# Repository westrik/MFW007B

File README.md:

# MFW007B
NA-01 Rev B (for JLCPCB assembly)

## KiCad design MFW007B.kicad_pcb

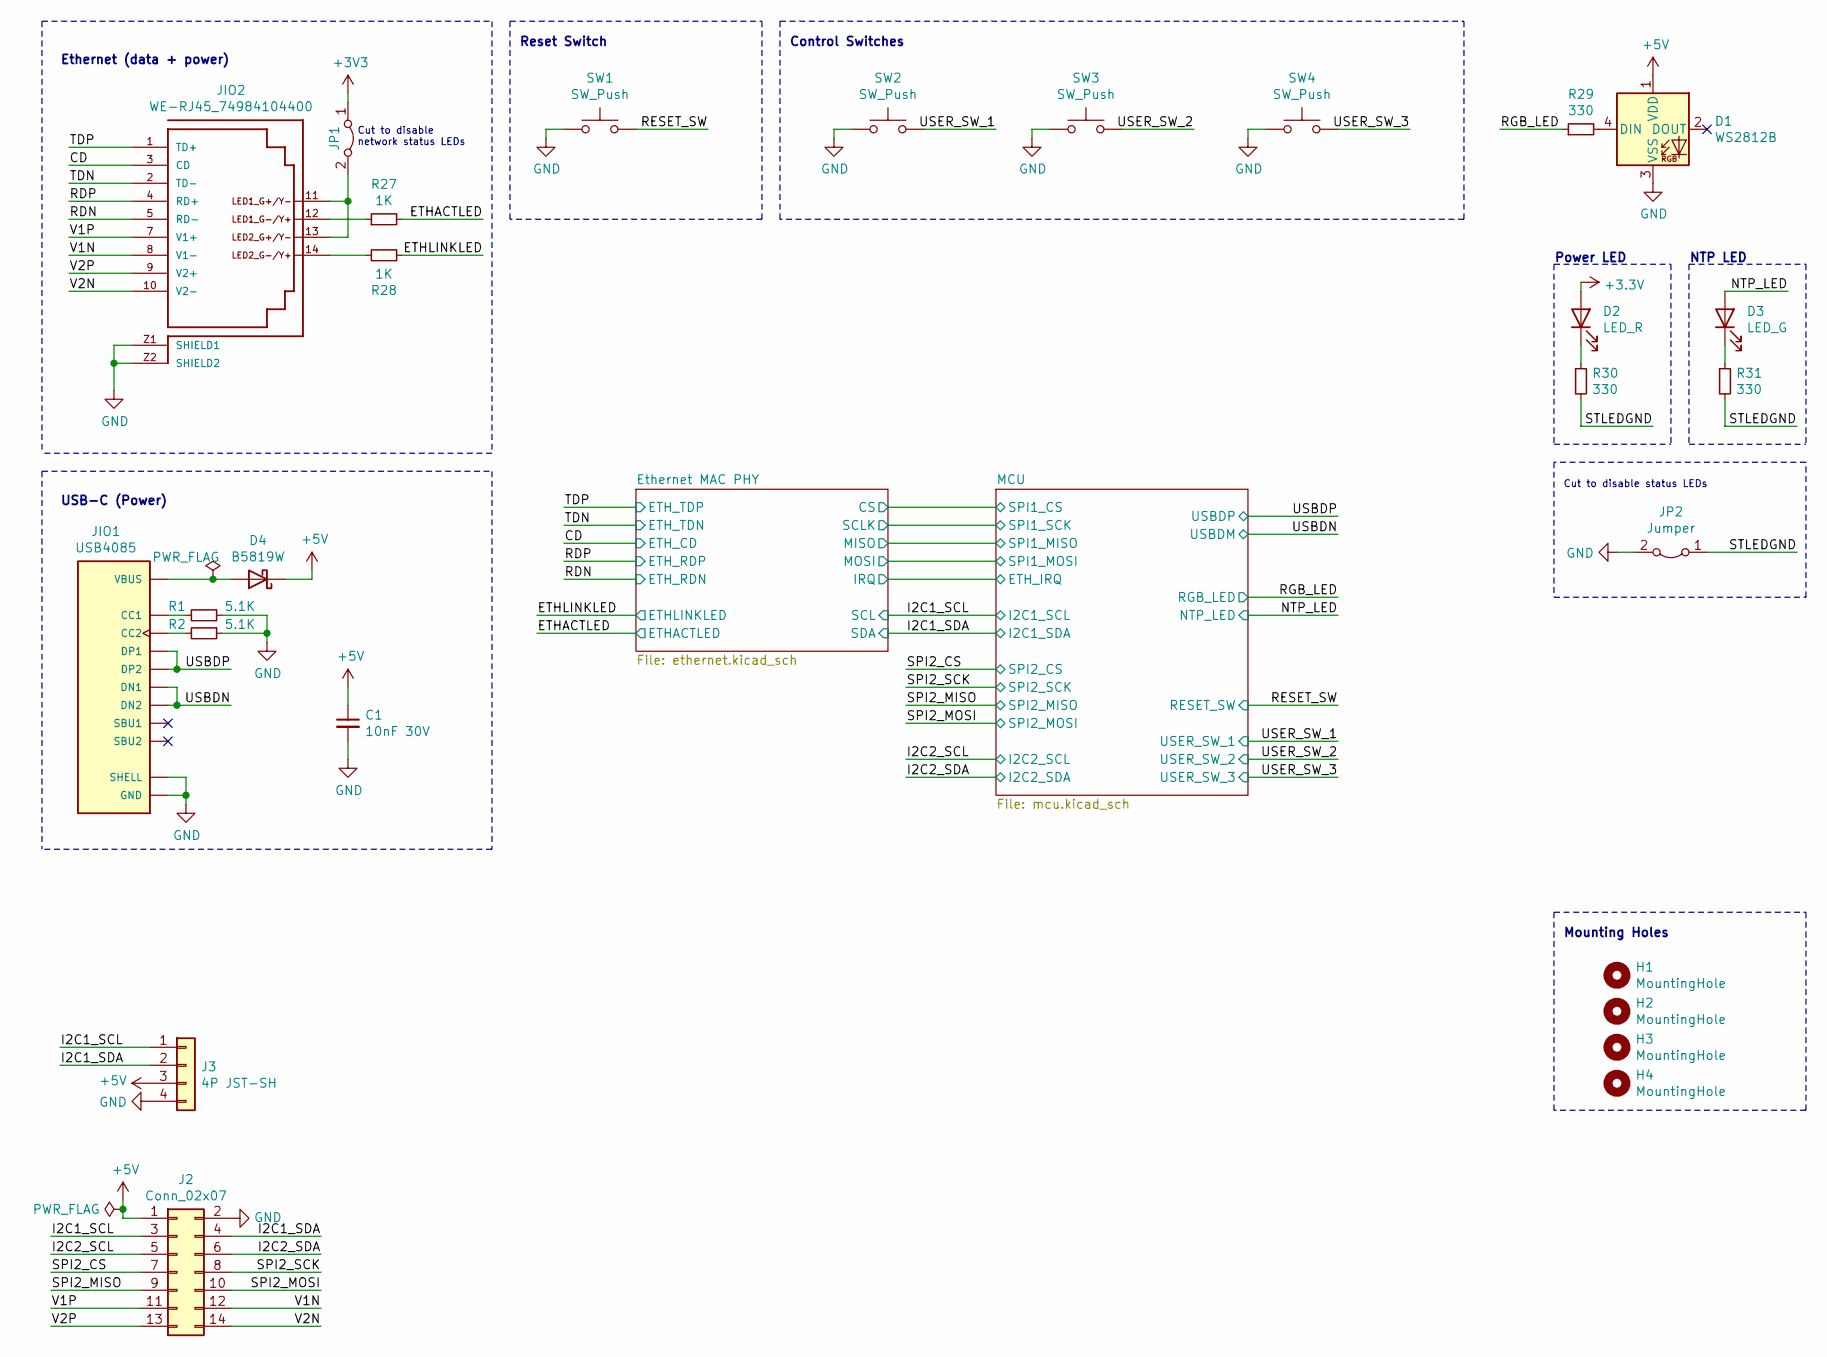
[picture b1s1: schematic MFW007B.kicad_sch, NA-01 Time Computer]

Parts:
C1: 10nF 30V; C_0805_2012Metric; LCSC Part Number C1710
D1: WS2812B; LED_WS2812B_PLCC4_5.0x5.0mm_P3.2mm; LCSC Part Number N/A
D2: LED_R; LED_0603_1608Metric; LCSC Part Number C2286
D3: LED_G; LED_0603_1608Metric; LCSC Part Number C72043
D4: B5819W; D_SOD-123; LCSC Part Number C8598
H1, H2, H3, H4: MountingHole; MountingHole_2.7mm_M2.5; LCSC Part Number N/A
J2: Conn_02x07; PinHeader_2x07_P2.54mm_Vertical; LCSC Part Number N/A
J3: 4P JST-SH; JST_SH_SM04B-SRSS-TB_1x04-1MP_P1.00mm_Horizontal; LCSC Part Number N/A
JIO1: USB4085; GCT_USB4085-GF-A_REVA; Manufacturer Part Number green/yellow-green/yellow; LCSC Part Number N/A
JIO2: WE-RJ45_74984104400; 74984104400; PART-NUMBER 74984104400; LCSC Part Number N/A
JP1, JP2: Jumper; SolderJumper-2_P1.3mm_Bridged_RoundedPad1.0x1.5mm; LCSC Part Number N/A
R1, R2: 5.1K; R_0402_1005Metric; LCSC Part Number C25905
R27, R28: 1K; R_0402_1005Metric
R29, R30, R31: 330; R_0402_1005Metric
SW1, SW2, SW3, SW4: SW_Push; PTS647SK38SMTR2LFS; LCSC Part Number N/A

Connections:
+5V: C1.1, D1.1 (VDD), D4.1 (K), J2.1, J3.3; also elsewhere on the board
/CD: JIO2.3 (CD); also elsewhere on the board
/ETHACTLED: R27.2; also elsewhere on the board
/ETHLINKLED: R28.1; also elsewhere on the board
/I2C1_SCL: J2.3, J3.1; also elsewhere on the board
/I2C1_SDA: J2.4, J3.2; also elsewhere on the board
/I2C2_SCL: J2.5; also elsewhere on the board
/I2C2_SDA: J2.6; also elsewhere on the board
/NTP_LED: D3.2 (A); also elsewhere on the board
/RDN: JIO2.5 (RD-); also elsewhere on the board
/RDP: JIO2.4 (RD+); also elsewhere on the board
/RESET_SW: SW1.2; also elsewhere on the board
/RGB_LED: R29.1; also elsewhere on the board
/SPI2_CS: J2.7; also elsewhere on the board
/SPI2_MISO: J2.9; also elsewhere on the board
/SPI2_MOSI: J2.10; also elsewhere on the board
/SPI2_SCK: J2.8; also elsewhere on the board
/STLEDGND: JP2.1 (A), R30.2, R31.2
/TDN: JIO2.2 (TD-); also elsewhere on the board
/TDP: JIO2.1 (TD+); also elsewhere on the board
/USBDN: JIO1.A7 (DN1), JIO1.B7 (DN2); also elsewhere on the board
/USBDP: JIO1.A6 (DP1), JIO1.B6 (DP2); also elsewhere on the board
/USER_SW_1: SW2.2; also elsewhere on the board
/USER_SW_2: SW3.2; also elsewhere on the board
/USER_SW_3: SW4.2; also elsewhere on the board
/V1N: J2.12, JIO2.8 (V1-)
/V1P: J2.11, JIO2.7 (V1+)
/V2N: J2.14, JIO2.10 (V2-)
/V2P: J2.13, JIO2.9 (V2+)
GND: C1.2, D1.3 (VSS), J2.2, J3.4, JIO1.A1 (GND), JIO1.A12 (GND), JIO1.B1 (GND), JIO1.B12 (GND), JIO1.P1 (SHELL), JIO1.P2 (SHELL), JIO1.P3 (SHELL), JIO1.P4 (SHELL), JIO2.Z1 (SHIELD1), JIO2.Z2 (SHIELD2), JP2.2 (B), R1.1, R2.1, SW1.1, SW2.1, SW3.1, SW4.1; also elsewhere on the board
unnamed: D1.4 (DIN), R29.2
unnamed: D2.1 (K), R30.1
unnamed: D3.1 (K), R31.1
unnamed: D4.2 (A), JIO1.A4 (VBUS), JIO1.A9 (VBUS), JIO1.B4 (VBUS), JIO1.B9 (VBUS)
unnamed: JIO1.A5 (CC1), R1.2
unnamed: JIO1.B5 (CC2), R2.2
unnamed: JIO2.11, JIO2.13, JP1.2 (B)
unnamed: JIO2.12, R27.1
unnamed: JIO2.14, R28.2
no_connect_(D1-Pad2): D1.2 (DOUT)
no_connect_(JIO1-PadA8): JIO1.A8 (SBU1)
no_connect_(JIO1-PadB8): JIO1.B8 (SBU2)

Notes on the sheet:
Ethernet (data + power)
USB-C (Power)
Cut to disable network status LEDs
Reset Switch
Control Switches
Power LED
Cut to disable status LEDs
Mounting Holes
NTP LED

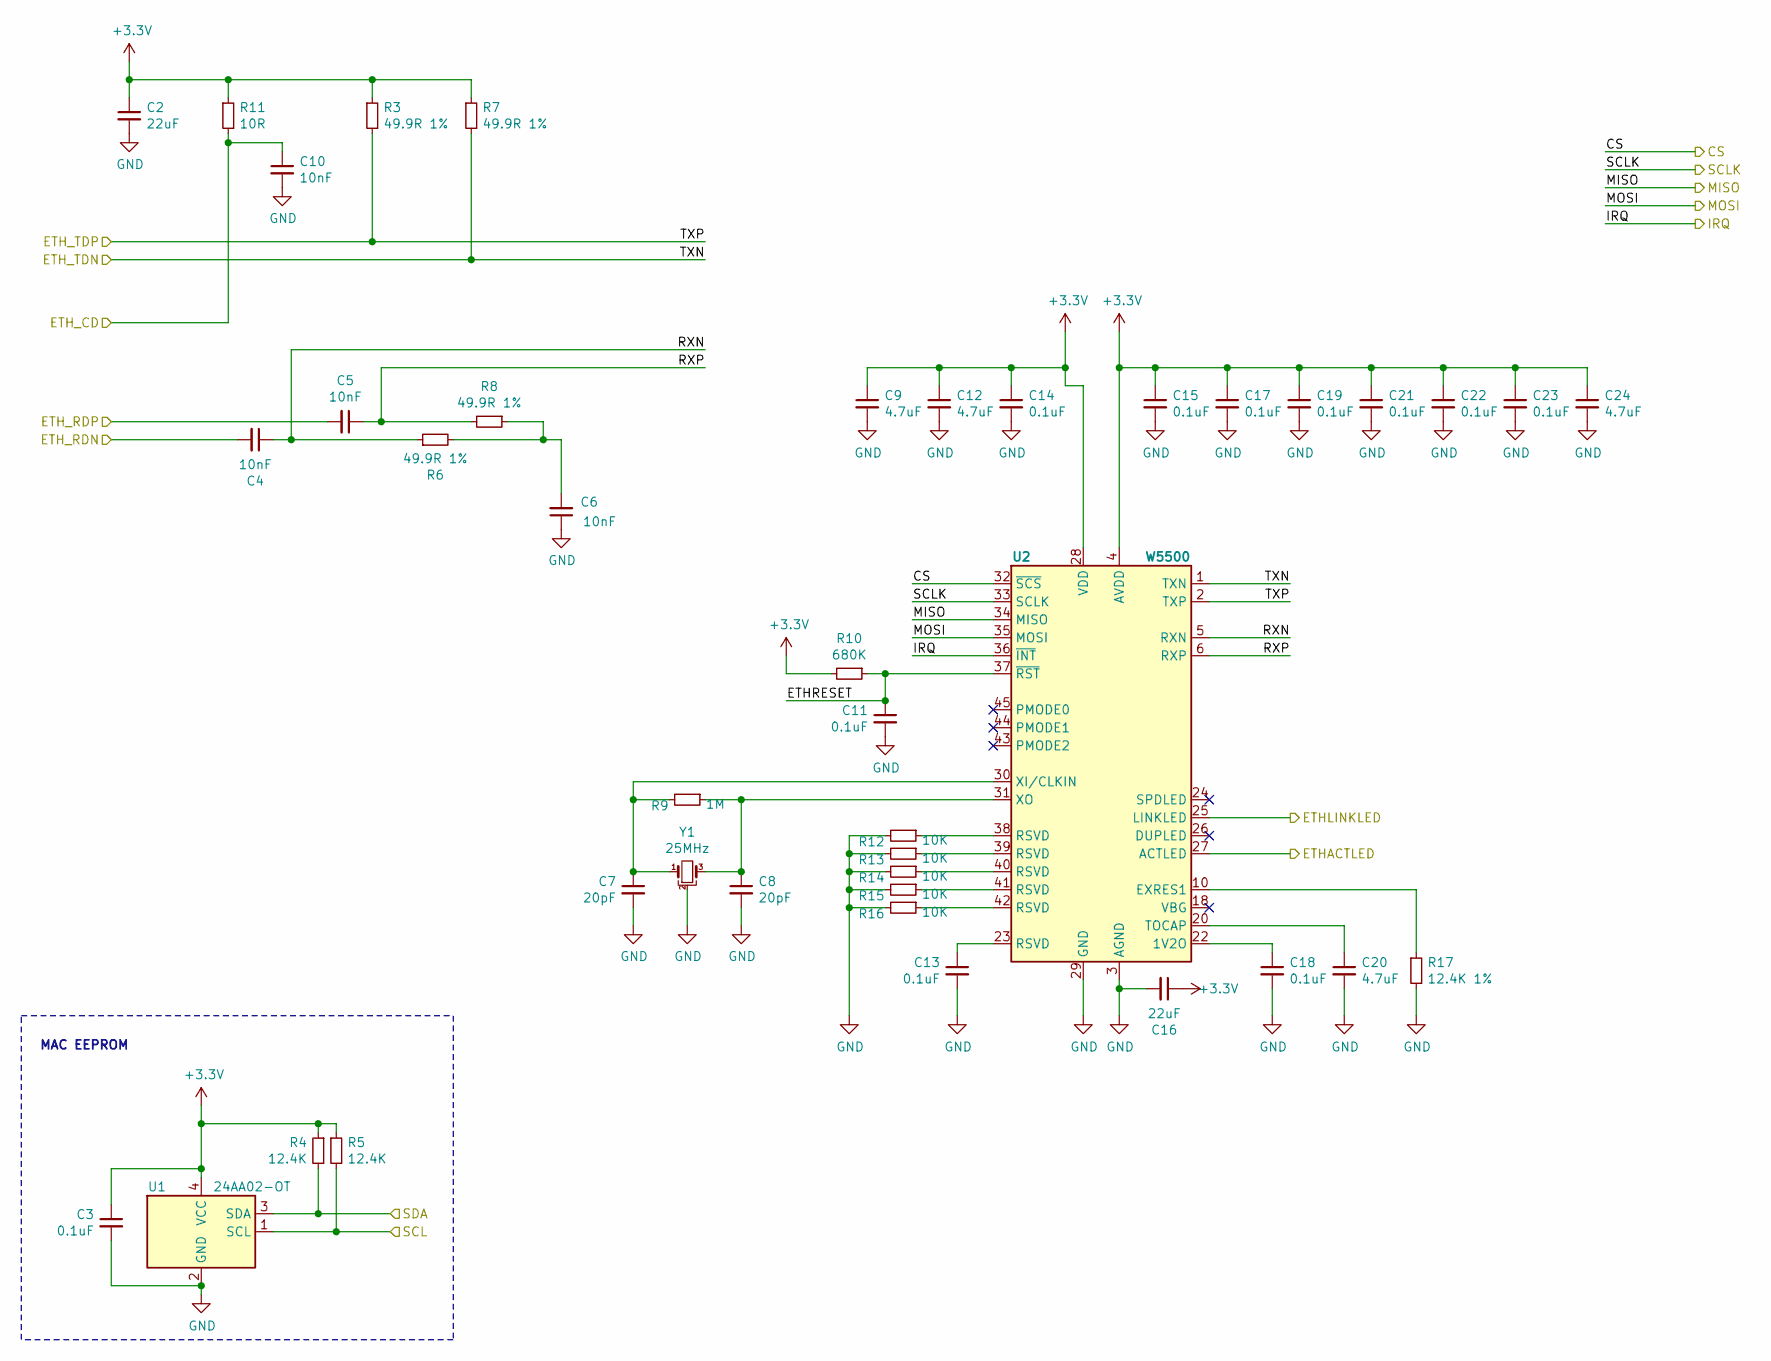
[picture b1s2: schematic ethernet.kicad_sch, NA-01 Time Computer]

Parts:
C2, C16: 22uF; C_0805_2012Metric; LCSC Part Number C59461
C3, C11, C13, C14, C15, C17, C18, C19, C21, C22, C23: 0.1uF; C_0402_1005Metric; LCSC Part Number C1525
C4, C5, C6, C10: 10nF; C_0402_1005Metric; LCSC Part Number C15195
C7, C8: 20pF; C_0402_1005Metric; LCSC Part Number C1554
C9, C12, C20, C24: 4.7uF; C_0402_1005Metric; LCSC Part Number C23733
R3, R6, R7, R8: 49.9R 1%; R_0402_1005Metric; LCSC Part Number C25120
R4, R5: 12.4K; R_0402_1005Metric
R9: 1M; R_0402_1005Metric
R10: 680K; R_0603_1608Metric
R11: 10R; R_0402_1005Metric
R12, R13, R14, R15, R16: 10K; R_0402_1005Metric
R17: 12.4K 1%; R_0402_1005Metric
U1: 24AA02-OT; SOT-23-5
U2: W5500; LQFP-48_7x7mm_P0.5mm
Y1: 25MHz; Crystal_SMD_3225-4Pin_3.2x2.5mm

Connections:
/CD: C10.1, R11.2; also elsewhere on the board
/ETHACTLED: U2.27 (ACTLED); also elsewhere on the board
/ETHLINKLED: U2.25 (LINKLED); also elsewhere on the board
/Ethernet MAC PHY/CS: U2.32 (~SCS); also elsewhere on the board
/Ethernet MAC PHY/ETHRESET: C11.1, R10.1, U2.37 (~RST)
/Ethernet MAC PHY/IRQ: U2.36 (~INT); also elsewhere on the board
/Ethernet MAC PHY/MISO: U2.34 (MISO); also elsewhere on the board
/Ethernet MAC PHY/MOSI: U2.35 (MOSI); also elsewhere on the board
/Ethernet MAC PHY/RXN: C4.1, R6.1, U2.5 (RXN)
/Ethernet MAC PHY/RXP: C5.1, R8.2, U2.6 (RXP)
/Ethernet MAC PHY/SCLK: U2.33 (SCLK); also elsewhere on the board
/I2C1_SCL: R5.2, U1.1 (SCL); also elsewhere on the board
/I2C1_SDA: R4.2, U1.3 (SDA); also elsewhere on the board
/RDN: C4.2; also elsewhere on the board
/RDP: C5.2; also elsewhere on the board
/TDN: R7.2, U2.1 (TXN); also elsewhere on the board
/TDP: R3.2, U2.2 (TXP); also elsewhere on the board
GND: C2.2, C3.2, C6.1, C7.2, C8.2, C9.2, C10.2, C11.2, C12.2, C13.2, C14.2, C15.2, C16.2, C17.2, C18.2, C19.2, C20.2, C21.2, C22.2, C23.2, C24.2, R12.2, R13.2, R14.2, R15.2, R16.2, R17.2, U1.2 (GND), U2.3 (AGND), U2.9 (AGND), U2.14 (AGND), U2.16 (AGND), U2.19 (AGND), U2.29 (GND), U2.48 (AGND), Y1.2; also elsewhere on the board
unnamed: C6.2, R6.2, R8.1
unnamed: C7.1, R9.2, U2.30 (XI/CLKIN), Y1.1
unnamed: C8.1, R9.1, U2.31 (XO), Y1.3
unnamed: C13.1, U2.23 (RSVD)
unnamed: C18.1, U2.22 (1V2O)
unnamed: C20.1, U2.20 (TOCAP)
unnamed: R12.1, U2.38 (RSVD)
unnamed: R13.1, U2.39 (RSVD)
unnamed: R14.1, U2.40 (RSVD)
unnamed: R15.1, U2.41 (RSVD)
unnamed: R16.1, U2.42 (RSVD)
unnamed: R17.1, U2.10 (EXRES1)
no_connect_(U1-Pad5): U1.5 (NC)
no_connect_(U2-Pad7): U2.7 (DNC)
no_connect_(U2-Pad12): U2.12 (NC)
no_connect_(U2-Pad13): U2.13 (NC)
no_connect_(U2-Pad18): U2.18 (VBG)
no_connect_(U2-Pad24): U2.24 (SPDLED)
no_connect_(U2-Pad26): U2.26 (DUPLED)
no_connect_(U2-Pad43): U2.43 (PMODE2)
no_connect_(U2-Pad44): U2.44 (PMODE1)
no_connect_(U2-Pad45): U2.45 (PMODE0)
no_connect_(U2-Pad46): U2.46 (NC)
no_connect_(U2-Pad47): U2.47 (NC)

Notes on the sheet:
MAC EEPROM

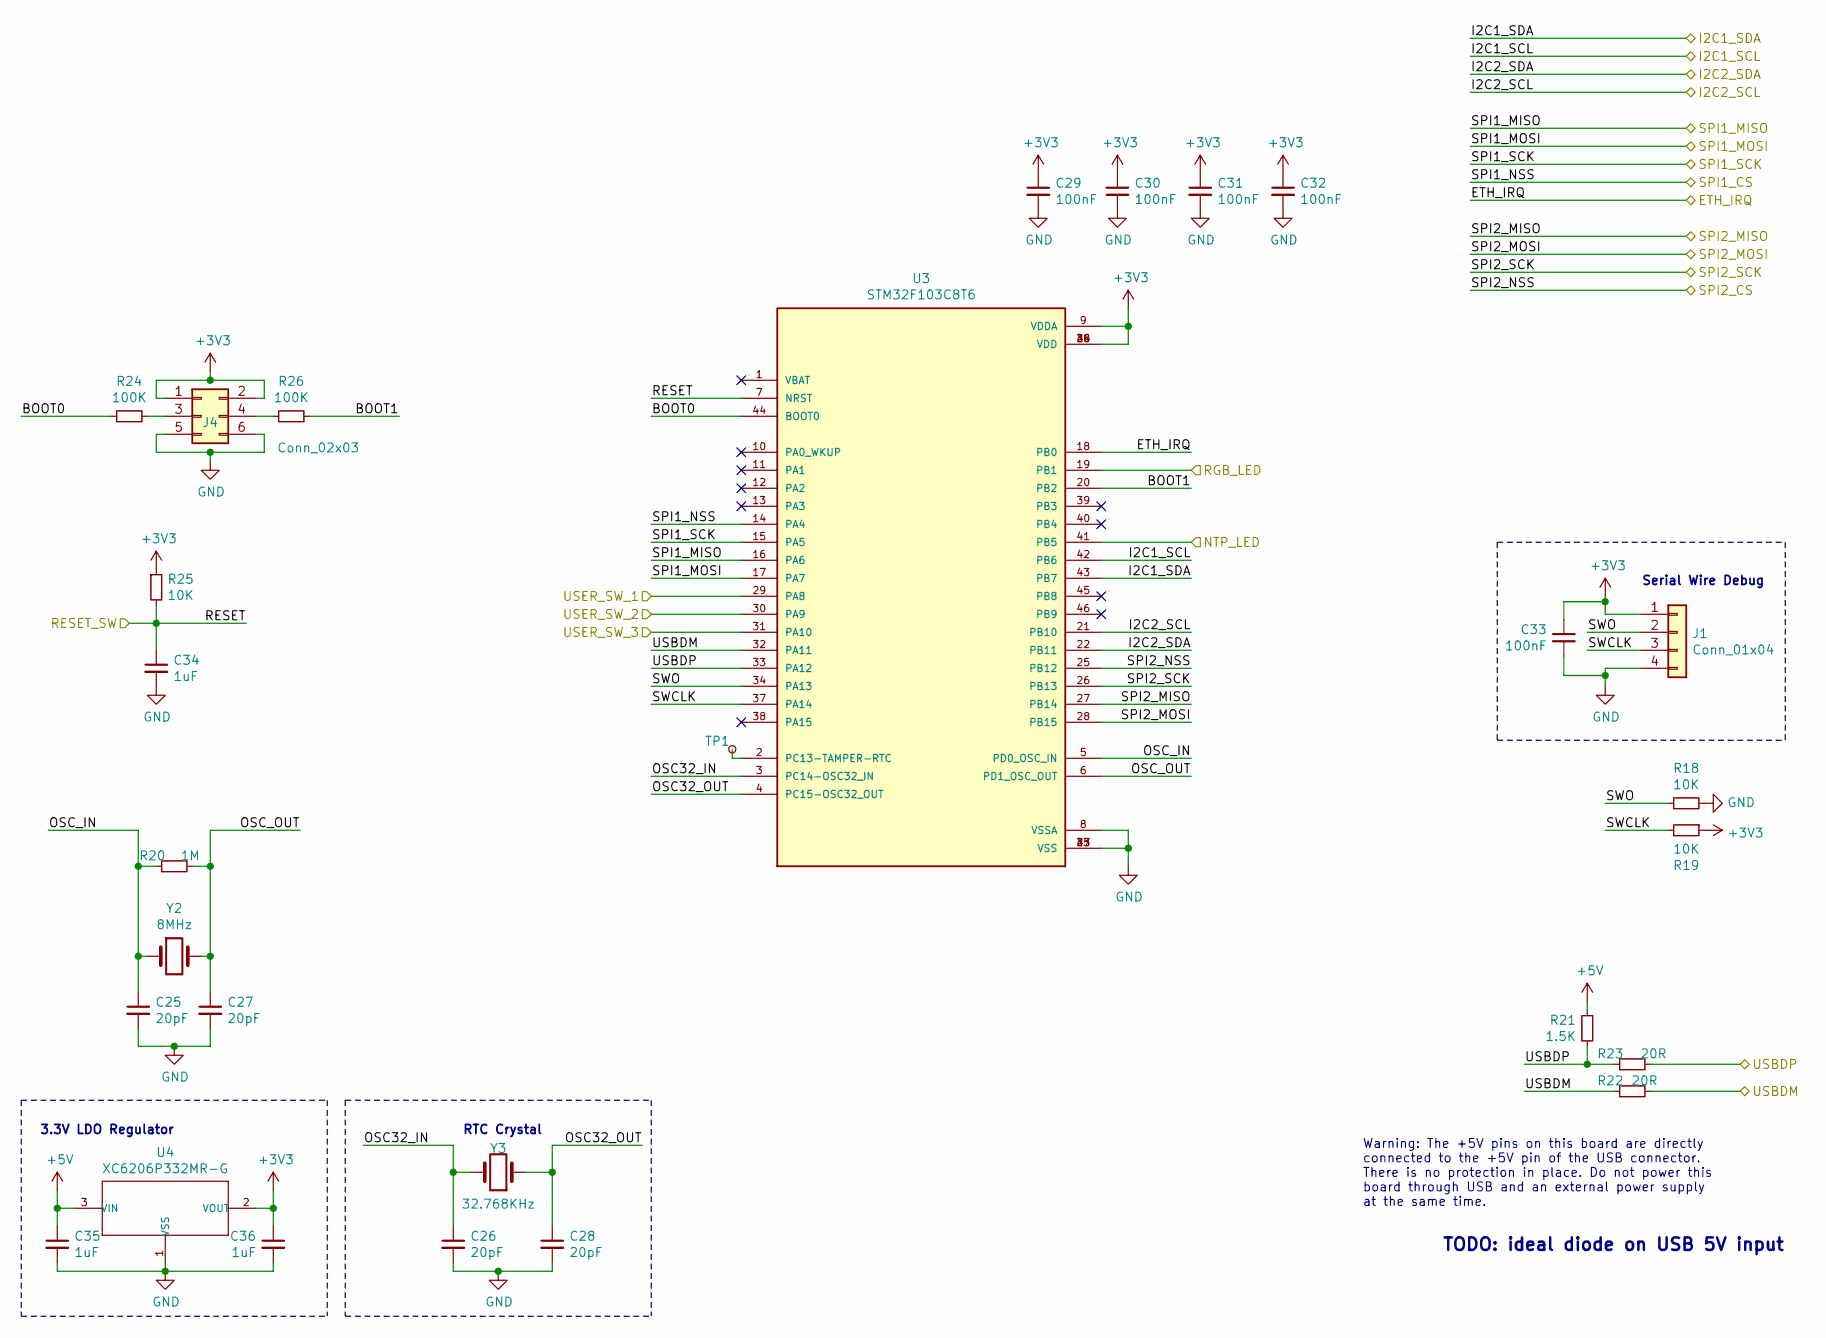
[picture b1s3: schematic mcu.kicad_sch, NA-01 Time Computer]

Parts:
C25, C26, C27, C28: 20pF; C_0402_1005Metric; LCSC Part Number C1554
C29, C30, C31, C32, C33: 100nF; C_0402_1005Metric; LCSC Part Number C1525
C34, C35, C36: 1uF; C_0402_1005Metric; LCSC Part Number C52923
J1: Conn_01x04; PinHeader_1x04_P2.54mm_Vertical; LCSC Part Number N/A
J4: Conn_02x03; PinHeader_2x03_P2.54mm_Vertical; LCSC Part Number N/A
R18, R19, R25: 10K; R_0402_1005Metric
R20: 1M; R_0402_1005Metric
R21: 1.5K; R_0402_1005Metric
R22, R23: 20R; R_0603_1608Metric
R24, R26: 100K; R_0402_1005Metric
TP1: TAMPER-RTC; TestPoint_Keystone_5010-5014_Multipurpose; LCSC Part Number N/A
U3: STM32F103C8T6; LQFP-48_7x7mm_P0.5mm; PARTREV 10
U4: XC6206P332MR-G; SOT-23; MPN XC6206P332MR-G; LCSC Part Number C5446
Y2: 8MHz; Crystal_SMD_5032-2Pin_5.0x3.2mm; Manufacturer Part Number X50328MSB2GI; LCSC Part Number C115962
Y3: 32.768KHz; Crystal_SMD_3215-2Pin_3.2x1.5mm; Manufacturer Part Number Q13FC1350000400; LCSC Part Number C32346

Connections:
+5V: C35.1, R21.1, U4.3 (VIN); also elsewhere on the board
/Ethernet MAC PHY/CS: U3.14 (PA4); also elsewhere on the board
/Ethernet MAC PHY/IRQ: U3.18 (PB0); also elsewhere on the board
/Ethernet MAC PHY/MISO: U3.16 (PA6); also elsewhere on the board
/Ethernet MAC PHY/MOSI: U3.17 (PA7); also elsewhere on the board
/Ethernet MAC PHY/SCLK: U3.15 (PA5); also elsewhere on the board
/I2C1_SCL: U3.42 (PB6); also elsewhere on the board
/I2C1_SDA: U3.43 (PB7); also elsewhere on the board
/I2C2_SCL: U3.21 (PB10); also elsewhere on the board
/I2C2_SDA: U3.22 (PB11); also elsewhere on the board
/MCU/BOOT0: R24.1, U3.44 (BOOT0)
/MCU/BOOT1: R26.2, U3.20 (PB2)
/MCU/OSC32_IN: C26.1, U3.3 (PC14-OSC32_IN), Y3.2
/MCU/OSC32_OUT: C28.1, U3.4 (PC15-OSC32_OUT), Y3.1
/MCU/OSC_IN: C25.1, R20.1, U3.5 (PD0_OSC_IN), Y2.1
/MCU/OSC_OUT: C27.1, R20.2, U3.6 (PD1_OSC_OUT), Y2.2
/MCU/SWCLK: J1.3, R19.2, U3.37 (PA14)
/MCU/SWO: J1.2, R18.1, U3.34 (PA13)
/NTP_LED: U3.41 (PB5); also elsewhere on the board
/RESET_SW: C34.1, R25.2, U3.7 (NRST); also elsewhere on the board
/RGB_LED: U3.19 (PB1); also elsewhere on the board
/SPI2_CS: U3.25 (PB12); also elsewhere on the board
/SPI2_MISO: U3.27 (PB14); also elsewhere on the board
/SPI2_MOSI: U3.28 (PB15); also elsewhere on the board
/SPI2_SCK: U3.26 (PB13); also elsewhere on the board
/USBDN: R22.1, R22.2, U3.32 (PA11); also elsewhere on the board
/USBDP: R21.2, R23.1, R23.2, U3.33 (PA12); also elsewhere on the board
/USER_SW_1: U3.29 (PA8); also elsewhere on the board
/USER_SW_2: U3.30 (PA9); also elsewhere on the board
/USER_SW_3: U3.31 (PA10); also elsewhere on the board
GND: C25.2, C26.2, C27.2, C28.2, C29.2, C30.2, C31.2, C32.2, C33.2, C34.2, C35.2, C36.2, J1.4, J4.5, J4.6, R18.2, U3.8 (VSSA), U3.23 (VSS), U3.35 (VSS), U3.47 (VSS), U4.1 (VSS); also elsewhere on the board
unnamed: J4.3, R24.2
unnamed: J4.4, R26.1
unnamed: TP1.1, U3.2 (PC13-TAMPER-RTC)
no_connect_(U3-Pad1): U3.1 (VBAT)
no_connect_(U3-Pad10): U3.10 (PA0_WKUP)
no_connect_(U3-Pad11): U3.11 (PA1)
no_connect_(U3-Pad12): U3.12 (PA2)
no_connect_(U3-Pad13): U3.13 (PA3)
no_connect_(U3-Pad38): U3.38 (PA15)
no_connect_(U3-Pad39): U3.39 (PB3)
no_connect_(U3-Pad40): U3.40 (PB4)
no_connect_(U3-Pad45): U3.45 (PB8)
no_connect_(U3-Pad46): U3.46 (PB9)

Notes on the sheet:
3.3V LDO Regulator
RTC Crystal
Warning: The +5V pins on this board are directly connected to the +5V pin of the USB connector. There is no protection in place. Do not power this board through USB and an external power supply at the same time.
Serial Wire Debug
TODO: ideal diode on USB 5V input

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
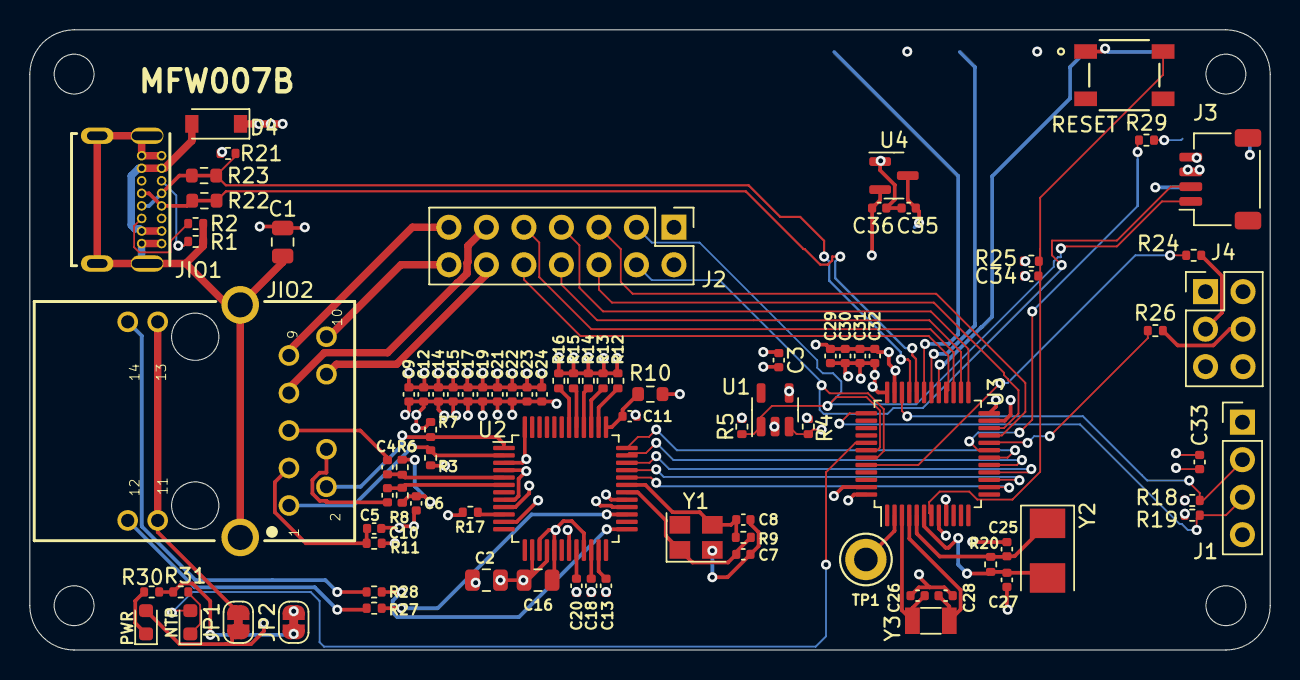
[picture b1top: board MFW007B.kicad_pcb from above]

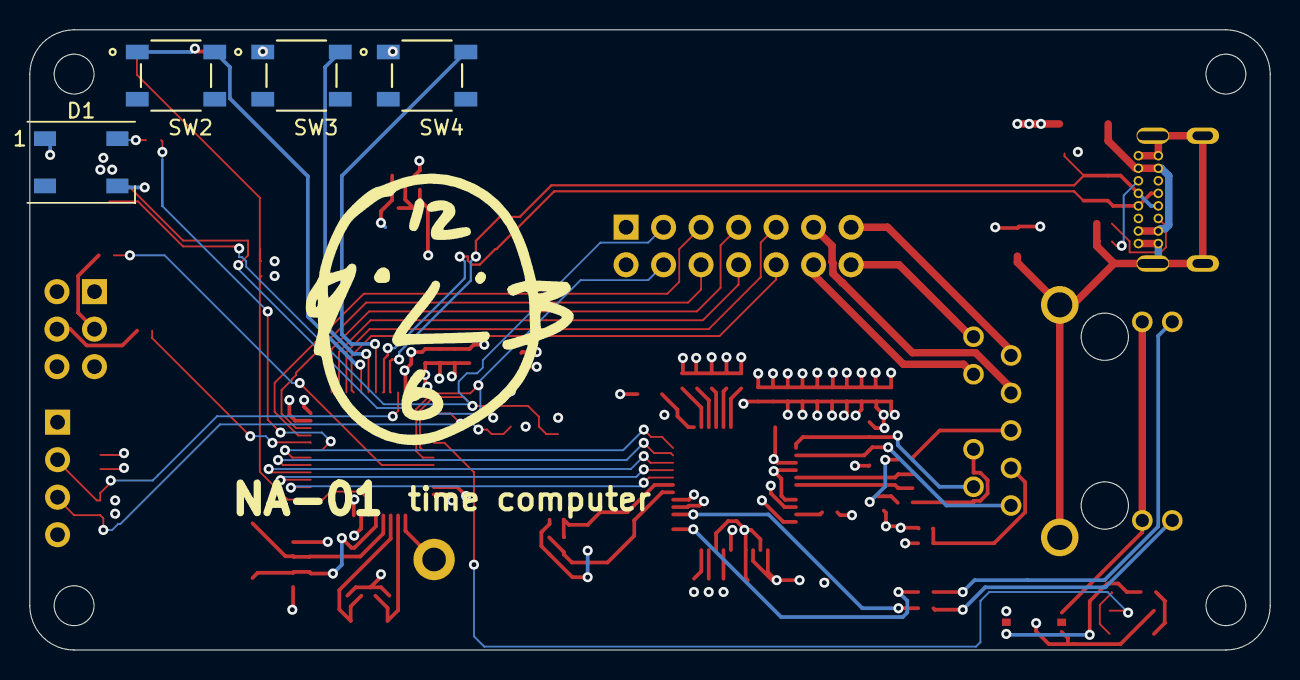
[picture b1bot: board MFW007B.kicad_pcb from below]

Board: 4 copper layers, 84.0 x 42.0 mm, 95 parts (4 on the bottom side), 71 nets.

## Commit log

2021-02-21 import relevant sections of MFW007A
2021-03-25 update 2021-03-25
2021-03-26 update PoE
2021-03-26 hook up STM32
2021-03-26 fix some lingering issues
2021-03-26 hook up mac eeprom to i2c
2021-03-27 fix label assignments and add 2x7 header
2021-03-28 finish porting blue pill schematic
2021-03-30 rough component placement
2021-03-30 refining component placement
2021-05-30 start routing
2021-05-30 rotate mcu
2021-05-30 remove duplicate components
2021-06-08 more routing
2021-06-08 add gnd + 3.3v fills
2021-06-08 connect to planes
2021-06-08 finetune routing
2021-06-08 fix DRC
2021-06-13 order PCB
2021-06-14 add some part numbers to schematic
2021-06-15 fix vias

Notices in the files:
parts and their libraries:
Copyright 2016 Accelerated Designs. All rights reserved.
